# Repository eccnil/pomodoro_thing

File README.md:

# Contador

Este proyecto permite fabricar un dispositivo creando una placa pcb, su circuito y su caja

El resultado es un aparato que puede servir como contador, como reloj de cocina o como metrónomo.
Aunque su funcionalidad no es su proprosito, se han añadido estas para dar vistosidad.

Conultese el [manual de operación](ManualUsuario.md) para saber como
operar el producto final

## Organización

Existen 3 carpetas, que recogen las principales partes de este proyecto:

| Carpeta          | Descripción              | Uso        |
| ---------------- | ------------------------ | ---------- |
| [shema](shema)   | Creación de la placa     | KiCad 9    |
| [case](case)     | Carcasa exterior         | Freecad 1  |
| [codigo](codigo) | Software (c++ / Arduino) | PlatformIO |

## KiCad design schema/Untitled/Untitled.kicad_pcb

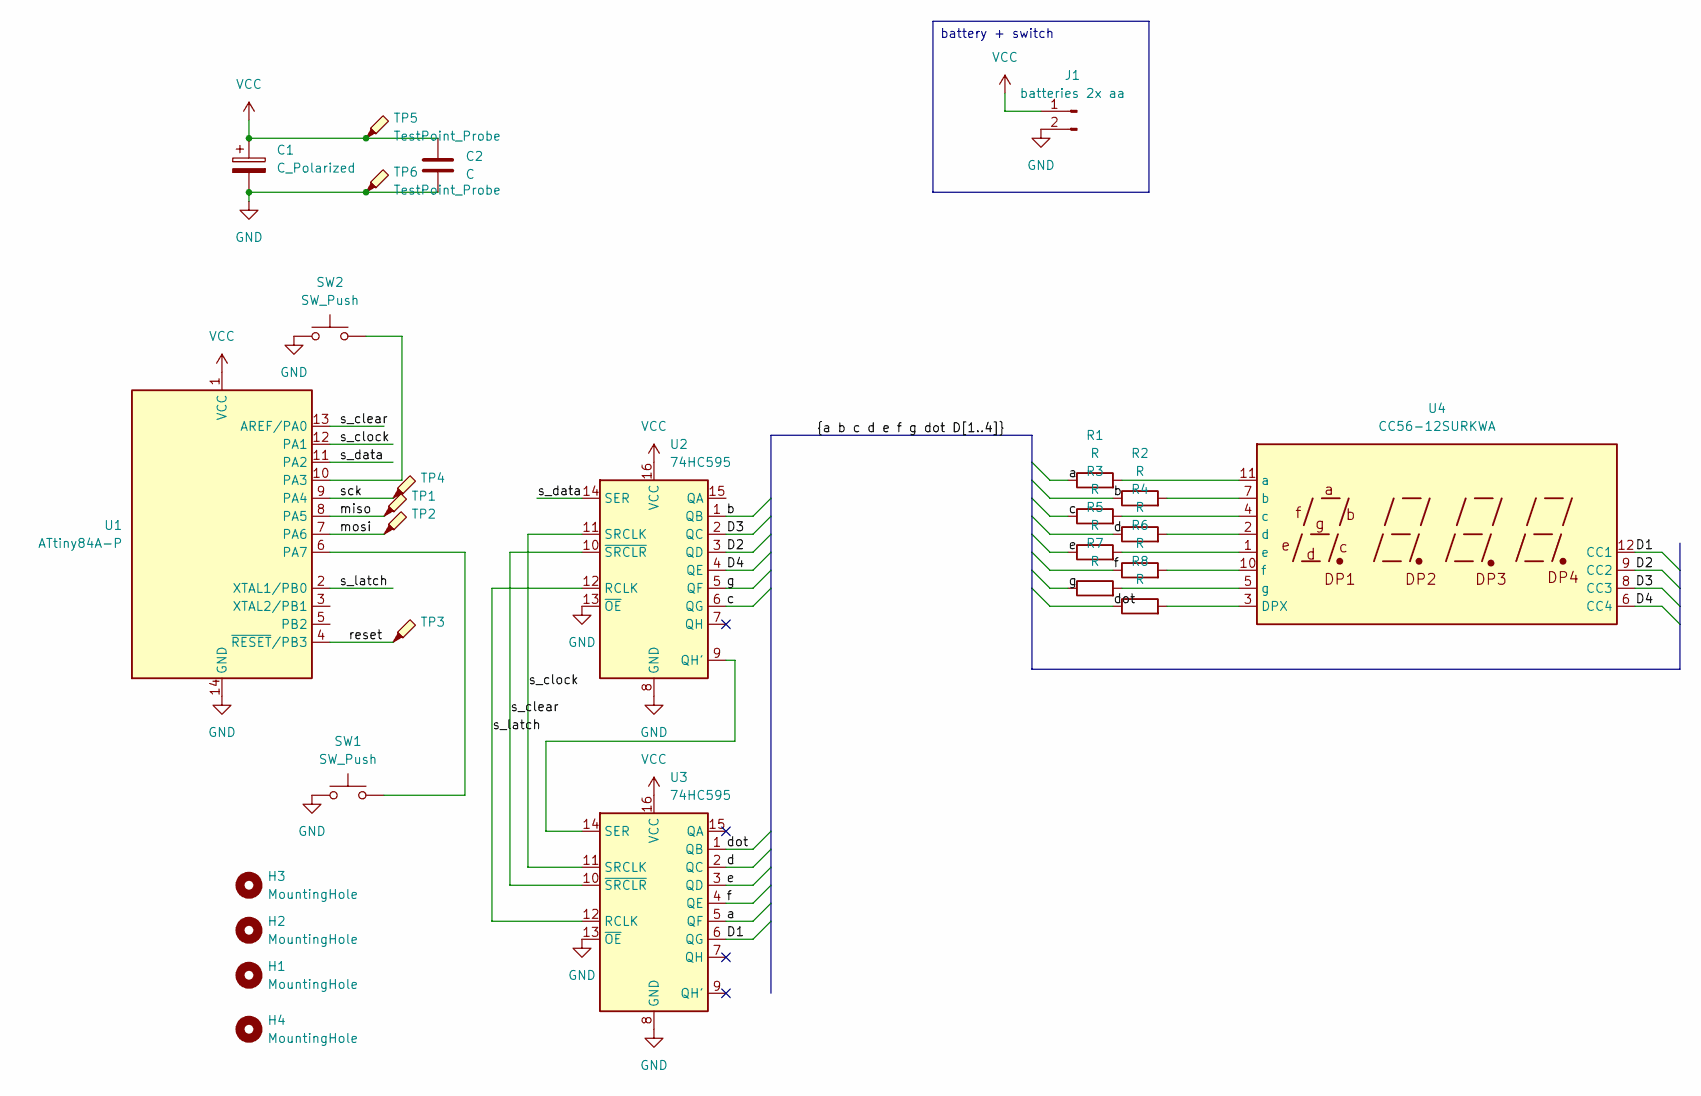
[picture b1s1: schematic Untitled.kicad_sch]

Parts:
C1: C_Polarized; CP_Radial_D5.0mm_P2.50mm
C2: C; C_Disc_D5.0mm_W2.5mm_P5.00mm
H1, H2, H3, H4: MountingHole; MountingHole_3.2mm_M3
J1: batteries 2x aa; SolderWire-0.1sqmm_1x02_P3.6mm_D0.4mm_OD1mm_Relief
R1, R2, R3, R4, R5, R6, R7, R8: R; R_1206_3216Metric_Pad1.30x1.75mm_HandSolder
SW1, SW2: SW_Push; SW_SPST_Omron_B3FS-101xP
TP1, TP2, TP3, TP4, TP5, TP6: TestPoint_Probe; Pin_D1.0mm_L10.0mm
U1: ATtiny84A-P; DIP-14_W7.62mm_SMDSocket_SmallPads
U2, U3: 74HC595; DIP-16_W7.62mm_SMDSocket_SmallPads
U4: CC56-12SURKWA; CA56-12SURKWA

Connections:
/D1: U3.6 (QG), U4.12 (CC1)
/D2: U2.3 (QD), U4.9 (CC2)
/D3: U2.2 (QC), U4.8 (CC3)
/D4: U2.4 (QE), U4.6 (CC4)
/a: R1.1, U3.5 (QF)
/b: R2.1, U2.1 (QB)
/c: R3.1, U2.6 (QG)
/d: R4.1, U3.2 (QC)
/dot: R8.1, U3.1 (QB)
/e: R5.1, U3.3 (QD)
/f: R6.1, U3.4 (QE)
/g: R7.1, U2.5 (QF)
/miso: TP1.1, U1.8 (PA5)
/mosi: TP2.1, U1.7 (PA6)
/reset: TP3.1, U1.4 (~RESET/PB3)
/s_clear: U1.13 (AREF/PA0), U2.10 (~SRCLR), U3.10 (~SRCLR)
/s_clock: U1.12 (PA1), U2.11 (SRCLK), U3.11 (SRCLK)
/s_data: U1.11 (PA2), U2.14 (SER)
/s_latch: U1.2 (XTAL1/PB0), U2.12 (RCLK), U3.12 (RCLK)
/sck: TP4.1, U1.9 (PA4)
GND: C1.2, C2.2, J1.2, SW1.1, SW2.1, TP6.1, U1.14 (GND), U2.8 (GND), U2.13 (~OE), U3.8 (GND), U3.13 (~OE)
unnamed: SW2.2, U1.10 (PA3)
unnamed: SW1.2, U1.6 (PA7)
unnamed: U2.9 (QH'), U3.14 (SER)
unnamed: R8.2, U4.3 (DPX)
unnamed: R1.2, U4.11 (a)
unnamed: R2.2, U4.7 (b)
unnamed: R3.2, U4.4 (c)
unnamed: R4.2, U4.2 (d)
unnamed: R5.2, U4.1 (e)
unnamed: R6.2, U4.10 (f)
unnamed: R7.2, U4.5 (g)
VCC: C1.1, C2.1, J1.1, TP5.1, U1.1 (VCC), U2.16 (VCC), U3.16 (VCC)

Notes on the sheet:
battery + switch

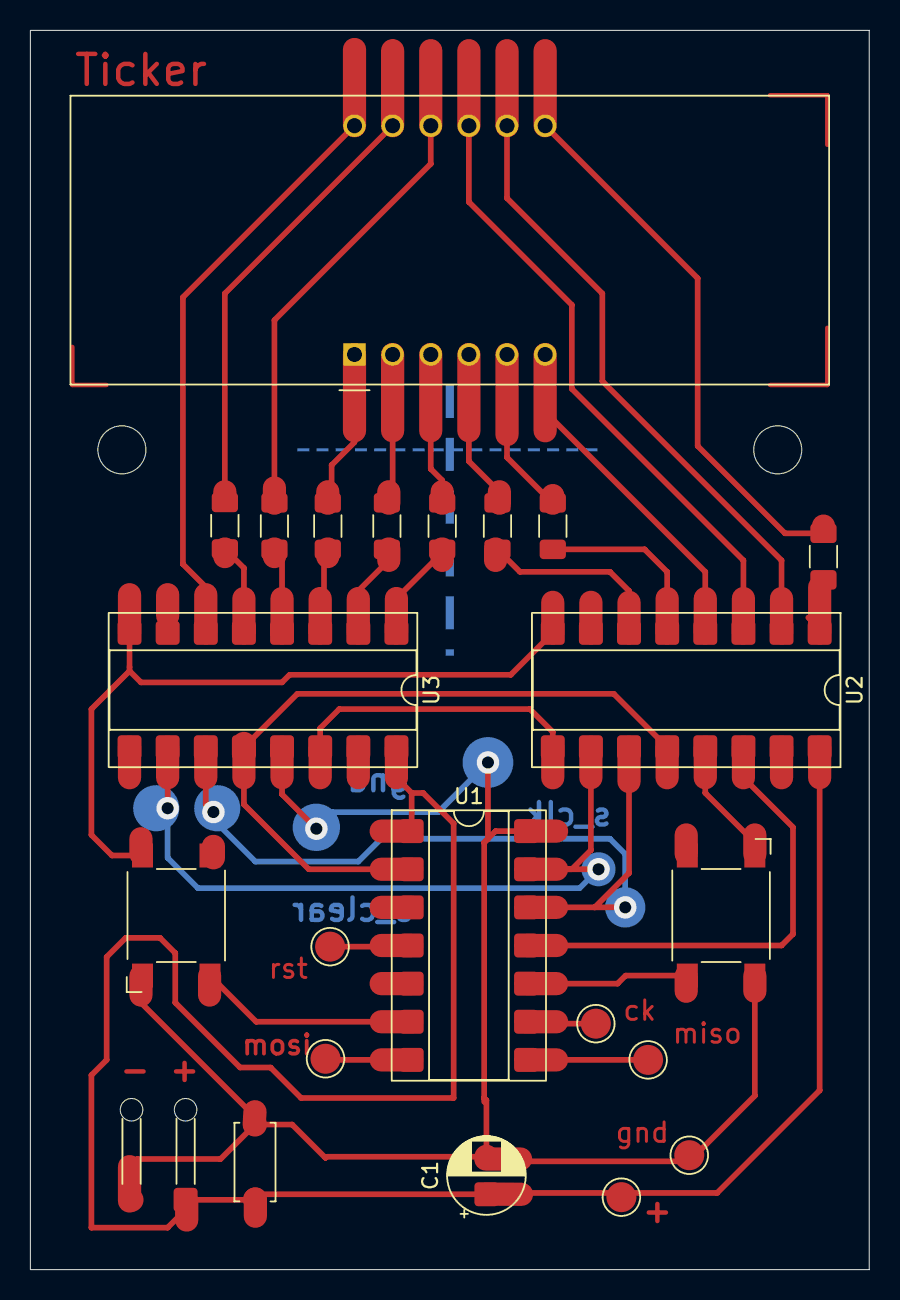
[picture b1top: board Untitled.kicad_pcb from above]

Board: 2 copper layers, 55.9 x 82.6 mm, 25 parts (0 on the bottom side), 33 nets.

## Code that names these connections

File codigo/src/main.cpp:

#include <Arduino.h>
#include <avr/io.h>
#include <devices/button.hpp>
#include <devices/segments.hpp>
#include <devices/shift_register.hpp>
#include <strategies/conter_strategy.hpp>
#include <strategies/metronome.hpp>
#include <strategies/pomodoro_strategy.hpp>
#include <strategy.hpp>
#include <util/delay.h>

// gpio PINs (using alternative order)
#define SER 8   // PA2 physical 11
#define RCLK 9  // PA1 physical 12
#define MR 10   // PA0 physical 13
#define LATCH 0 // PB0 physical 2

#define BUTTON_A 7 // PA3 physical 10
#define BUTTON_B 3 // PA7 Physical 6

// global variables
Strategy *strategy;

// shiftRegiseter that drives the display inputs
shiftRegisterPins srPins = {
    .latch = LATCH, .data = SER, .clock = RCLK, .clear = MR};
ShiftRegister shift_register = ShiftRegister(srPins, BITS_TO_WRITE);

// display (4digits x 7 sgements + dot)
Segments display = Segments(shift_register);

// press button_a (right one)
Button button_a = Button(BUTTON_A);
void b_a() {
  if (strategy != NULL)
    strategy->button_a_tap();
}

// press button_a (left one)
Button button_b = Button(BUTTON_B);
void b_b() {
  if (strategy != NULL)
    strategy->button_b_tap();
}

#define DEVICE_QUANTITY 3
Device *devices[DEVICE_QUANTITY] = {&display, &button_a, &button_b};

void setup() {
  // init devices
  for (int i = 0; i < DEVICE_QUANTITY; i++) {
    devices[i]->init();
  }

  // check buttons to decide the functionality to be loaded
  button_a.poll();
  button_b.poll();
  if (button_b.is_pressed()) {
    strategy = (Strategy *)new CounterStrategy(button_a, button_b);
  } else if (button_a.is_pressed()) {
    strategy = (Strategy *)new Metronome();
  } else {
    strategy = (Strategy *)new PomodoroStrategy();
  }

  // set buttons actions to the selected functionality
  button_b.set_on_tap(b_b);
  button_a.set_on_tap(b_a);
}

void loop() {
  // update all devices
  for (int i = 0; i < DEVICE_QUANTITY; i++) {
    devices[i]->poll();
  };

  // update strategy
  strategy->display(display);
}

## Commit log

2025-08-05 empty source project
2025-08-05 empty schematics project
2025-08-05 configuracion para arduino as isp
2025-08-06 fuses
2025-08-06 code v1
2025-08-06 delays
2025-08-06 version funcional 1
2025-08-06 button prototype
2025-08-07 surrounding circuits battery, capacitors, probes, etc
2025-08-07 pcb with display
2025-08-07 ultimos toques a la pcb
2025-08-07 segments
2025-08-07 nueva estructura de mapas de bits
2025-08-07 pcb que se realizará
2025-08-07 pines y mapas de la pcb
    el codigo hasta ahora tenia los pines y mapas de la panadera
2025-08-08 agujeros visibles
2025-08-08 corregidos los pines para los nuevos fuses
2025-08-08 la versión 2
2025-08-09 device
2025-08-09 shift register
2025-08-10 segment class
2025-08-10 clase imprimiendo numeros
2025-08-11 device list usage
2025-08-11 button
2025-08-11 refactor segments
2025-08-11 small refactor
2025-08-11 3dexport
2025-08-11 counter case
2025-08-11 all components to be enclosed
2025-08-12 cambiado el interruptor
2025-08-13 upper part of the case
2025-08-13 upper part of the case completed
2025-08-14 bottomcase
2025-08-14 buttons
2025-08-15 final design
2025-08-15 construcción
2025-08-16 construction
2025-08-24 limaduras
2025-08-27 pomodoro class as imported
2025-08-28 unit testing
2025-08-28 button things
2025-08-28 ready to test it
2025-09-05 reset when ringing
2025-09-05 strategies
2025-09-06 fixed stragegy selection
2025-09-06 include remmoved
2025-09-06 package reorganization
2025-09-06 removed compose digit
2025-09-06 exhaustive switch
2025-09-06 prepared for multi tests
2025-09-06 undo
2025-09-06 tempo class & test
2025-09-07 unsigned vars
2025-09-07 metronome strategy
2025-09-07 FIXME: el metronomo va el doble de rápido
2025-09-07 assigned strategy to button A
2025-09-07 using heap to load strategies
    instead of loading all strategies and using the selected, now we only
    load the selected
2025-09-07 warning removal
2025-09-07 summary
2025-09-08 manual de usuario
2025-09-09 foldable case
2025-09-09 correcciones post-maqueta de cartulina
2025-09-10 normal y mirror
